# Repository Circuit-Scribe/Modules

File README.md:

Modules
=======

Eagle files for all Circuit Scribe modules!

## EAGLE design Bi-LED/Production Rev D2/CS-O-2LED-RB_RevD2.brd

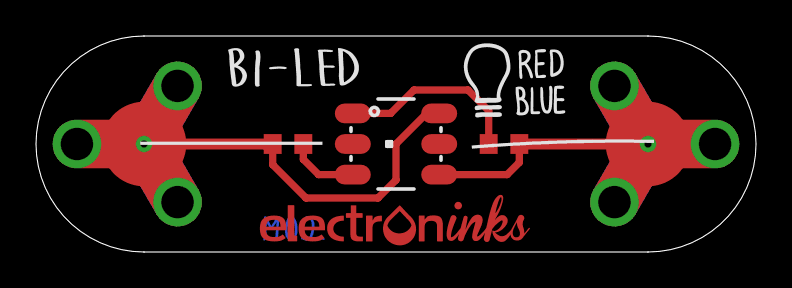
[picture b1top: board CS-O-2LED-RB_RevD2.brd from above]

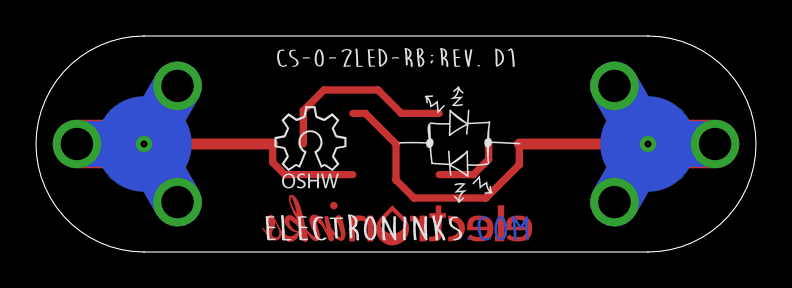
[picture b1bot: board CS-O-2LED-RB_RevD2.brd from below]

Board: 2 copper layers, 40.0 x 12.0 mm, 9 parts (3 on the bottom side), 4 nets.

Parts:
LED1: LED-TRICOLOR-5050NO_IC; LED-TRICOLOR-5050
R2-BLUE: 3.3k 5%; R0603
R_RED: 2.2k 5%; R0603
U$1, U$2: ROUND-12MM-FOOT-1.8MM; ROUND-12MM-FOOT
U$4: ELECTRONINKS_LOGO_15MM
U$5: ELECTRONINKS_COM_15MM
U$7: OSHW_4MM; OHSW_4MM
U$8: CS_O_2LED_RB

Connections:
unnamed: LED1.1, R2-BLUE.1, U$1.P$1, U$1.P$2, U$1.P$3, U$1.P$4, U$1.P$5
unnamed: LED1.6, R_RED.2
unnamed: LED1.3, R_RED.1, U$2.P$1
unnamed: LED1.4, R2-BLUE.2

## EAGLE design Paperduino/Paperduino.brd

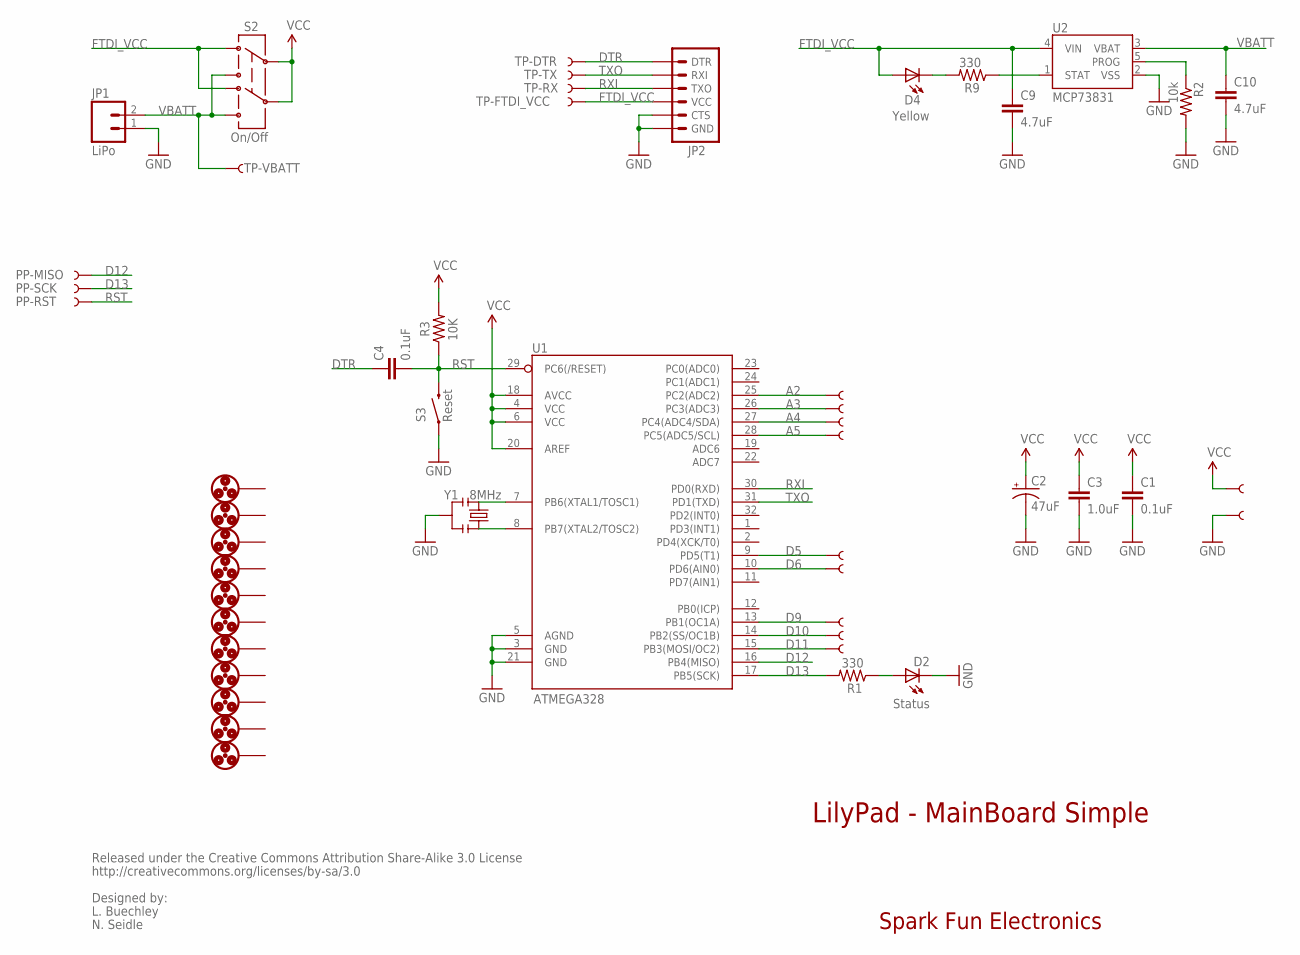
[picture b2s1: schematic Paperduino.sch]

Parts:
A2/16, A3/17, A4/18, A5/19: SEWTAP9; PETAL-LONG-1-2SIDE
C1, C4: 0.1uF; 0402-CAP
C2: 47uF; EIA3528
C3: 1.0uF; 0402-CAP
C9, C10: 4.7uF; 0402-CAP
D2: Status; LED-0603
D4: Yellow; LED-0603
JP1: LiPo; JST-2-SMD
JP2: ARDUINO_SERIAL_PROGRAMSMD; 1X06-SMD
PP-MISO: TEST-POINT3X5; PAD.03X.05
PP-RST: TEST-POINT3X5; PAD.03X.05
PP-SCK: TEST-POINT3X5; PAD.03X.05
R1, R9: 330; 0402-RES
R2: 10k; 0402-RES
R3: 10K; 0402-RES
S2: On/Off; AYZ0202
S3: Reset; TACTILE_SWITCH_SMD
TP-DTR: TEST-POINT3X5; PAD.03X.05
TP-FTDI_VCC: TEST-POINT3X5; PAD.03X.05
TP-RX: TEST-POINT3X5; PAD.03X.05
TP-TX: TEST-POINT3X5; PAD.03X.05
TP-VBATT: TEST-POINT3X5; PAD.03X.05
U1: ATMEGA328; TQFP32-08
U2: MCP73831; SOT23-5
U$1, U$2, U$3, U$5, U$6, U$7, U$8, U$9, U$10, U$11, U$12: ROUND-12MM-FOOT-1.8MM; ROUND-12MM-FOOT
U$4, U$35, U$37, U$39, U$41, U$43, U$45: SEWTAP9; PETAL-LONG-1-2SIDE
Y1: 8MHz; RESONATOR-SMD

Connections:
A2: A2/16.1, U1.25 (PC2(ADC2))
A3: A3/17.1, U1.26 (PC3(ADC3))
A4: A4/18.1, U1.27 (PC4(ADC4/SDA))
A5: A5/19.1, U1.28 (PC5(ADC5/SCL))
D5: U1.9 (PD5(T1)), U$41.1
D6: U1.10 (PD6(AIN0)), U$35.1
D9: U1.13 (PB1(OC1A)), U$37.1
D10: U1.14 (PB2(SS/OC1B)), U$39.1
D11: U1.15 (PB3(MOSI/OC2)), U$4.1
D12: PP-MISO.P$1, U1.16 (PB4(MISO))
D13: PP-SCK.P$1, R1.2, U1.17 (PB5(SCK))
DTR: C4.1, JP2.1 (DTR), TP-DTR.P$1
FTDI_VCC: C9.1, D4.A, JP2.4 (VCC), S2.3 (1), S2.6 (4), TP-FTDI_VCC.P$1, U2.4 (VIN)
GND: C1.2, C2.C (-), C3.2, C9.2, C10.2, D2.C, JP1.1, JP2.5 (CTS), JP2.6 (GND), R2.2, S3.1, U1.3 (GND), U1.5 (AGND), U1.21 (GND), U2.2 (VSS), U$43.1, Y1.2
unnamed: U1.7 (PB6(XTAL1/TOSC1)), Y1.1
unnamed: D2.A, R1.1
unnamed: U1.8 (PB7(XTAL2/TOSC2)), Y1.3
unnamed: D4.C, R9.2
PROG: R2.1, U2.5 (PROG)
RST: C4.2, PP-RST.P$1, R3.1, S3.3 (2), U1.29 (PC6(/RESET))
RXI: JP2.3 (TXO), TP-RX.P$1, U1.30 (PD0(RXD))
STAT: R9.1, U2.1 (STAT)
TXO: JP2.2 (RXI), TP-TX.P$1, U1.31 (PD1(TXD))
VBATT: C10.1, JP1.2, S2.1 (3), S2.4 (6), TP-VBATT.P$1, U2.3 (VBAT)
VCC: C1.1, C2.A (+), C3.1, R3.2, S2.2, S2.5, U1.4 (VCC), U1.6 (VCC), U1.18 (AVCC), U1.20 (AREF), U$45.1

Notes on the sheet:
LilyPad - MainBoard Simple
Spark Fun Electronics
Released under the Creative Commons Attribution Share-Alike 3.0 License
http://creativecommons.org/licenses/by-sa/3.0
Designed by:
L. Buechley
N. Seidle

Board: 2 copper layers, 49 parts (0 on the bottom side), 25 nets, no tracks yet.

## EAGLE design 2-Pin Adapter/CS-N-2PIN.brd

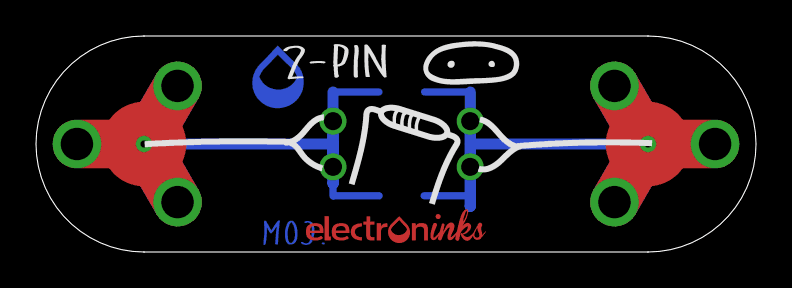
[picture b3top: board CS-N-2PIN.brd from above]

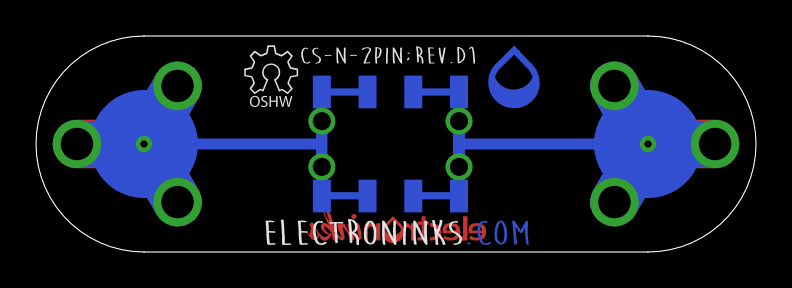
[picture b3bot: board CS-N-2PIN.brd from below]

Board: 2 copper layers, 40.0 x 12.0 mm, 8 parts (5 on the bottom side), 2 nets.

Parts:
U$1, U$2: ROUND-12MM-FOOT-1.8MM; ROUND-12MM-FOOT
U$3: DROPLET_LOGO_3MM
U$4: OSHW_3MM
U$5: ELECTRONINKS_COM_15MM
U$6: ELECTRONINKS_LOGO_10MM
U$7: C_N_2PIN; CS_N_2PIN
U$8: 966206-2000-AR-PR-SOCKET-2-PIN-6POS; 966206-2000-AR-PR-6-POS-THROUGH-HOLE

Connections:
unnamed: U$2.P$1, U$8.P$5, U$8.P$11, U$8.P$111, U$8.P$55555
unnamed: U$1.P$1, U$8.P$4, U$8.P$8

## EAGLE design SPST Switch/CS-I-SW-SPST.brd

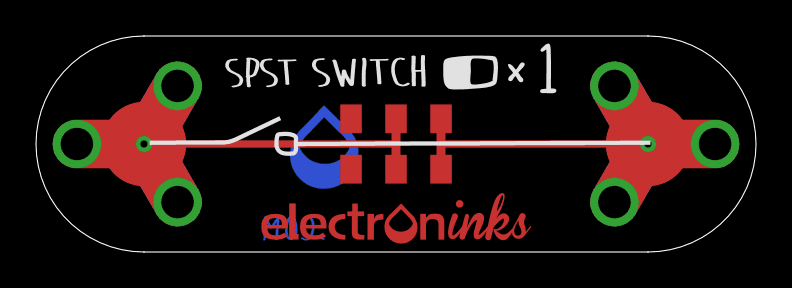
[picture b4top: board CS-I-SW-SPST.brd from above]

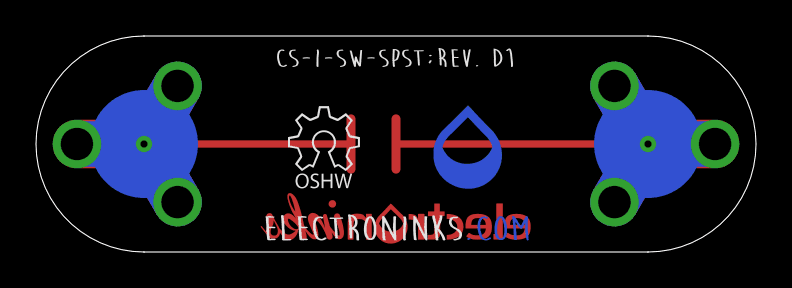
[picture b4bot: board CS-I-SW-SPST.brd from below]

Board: 2 copper layers, 40.0 x 12.0 mm, 8 parts (4 on the bottom side), 2 nets.

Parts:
U$1, U$2: ROUND-12MM-FOOT-1.8MM; ROUND-12MM-FOOT
U$3: ELECTRONINKS_LOGO_15MM
U$4: ELECTRONINKS_COM_15MM
U$5: CL-SB-22A-02T-SLIDE-SWITCH-TUCKED-PADS; CL-SB-22A-02T-DPDT-COMPACT-SWITCH
U$6: DROPLET_LOGO_4MM
U$7: OSHW_4MM; OHSW_4MM
U$8: CS_I_SW_SPST

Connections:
unnamed: U$1.P$1, U$5.P$1, U$5.P$4
unnamed: U$2.P$1, U$5.P$2, U$5.P$5

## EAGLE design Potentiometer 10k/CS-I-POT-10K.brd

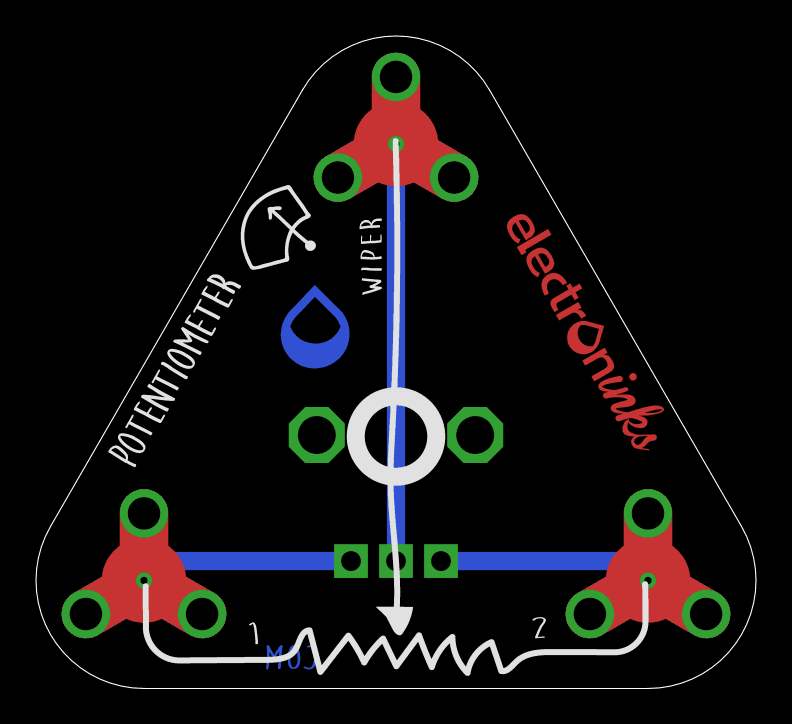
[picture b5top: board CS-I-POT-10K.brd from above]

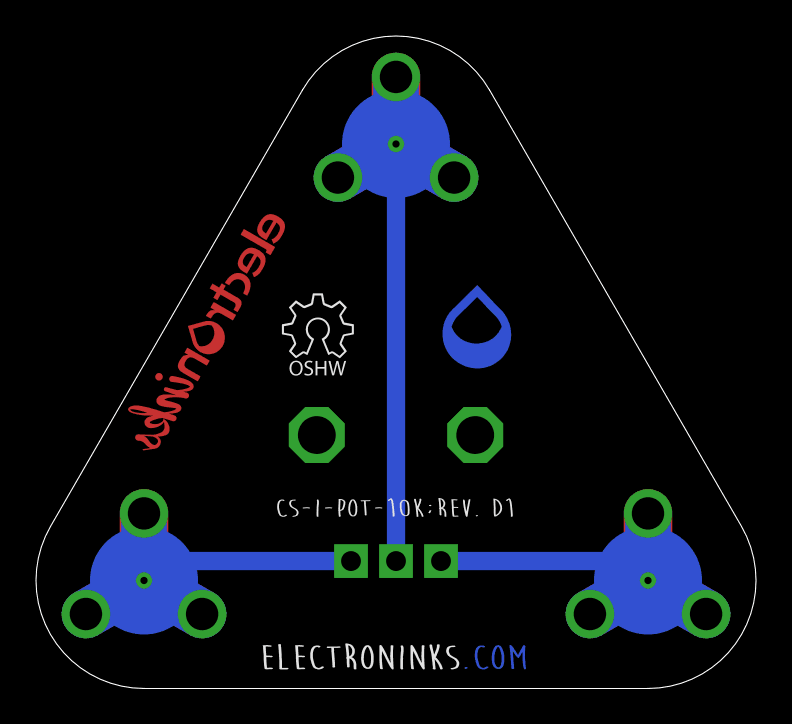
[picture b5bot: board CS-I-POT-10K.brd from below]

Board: 2 copper layers, 40.0 x 36.2 mm, 9 parts (4 on the bottom side), 3 nets.

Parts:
RV1: ALPS_POT
U$1, U$2, U$3: ROUND-12MM-FOOT-1.8MM; ROUND-12MM-FOOT
U$4: ELECTRONINKS_LOGO_15MM
U$5: ELECTRONINKS_COM_15MM
U$6: DROPLET_LOGO_4MM
U$7: OSHW_4MM; OHSW_4MM
U$8: CS_I_POT_10K

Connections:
unnamed: RV1.P$3, U$1.P$1, U$1.P$2, U$1.P$3, U$1.P$4, U$1.P$5
unnamed: RV1.P$1, U$3.P$1, U$3.P$2, U$3.P$3, U$3.P$4, U$3.P$5
unnamed: RV1.P$2, U$2.P$1, U$2.P$2, U$2.P$3, U$2.P$4, U$2.P$5

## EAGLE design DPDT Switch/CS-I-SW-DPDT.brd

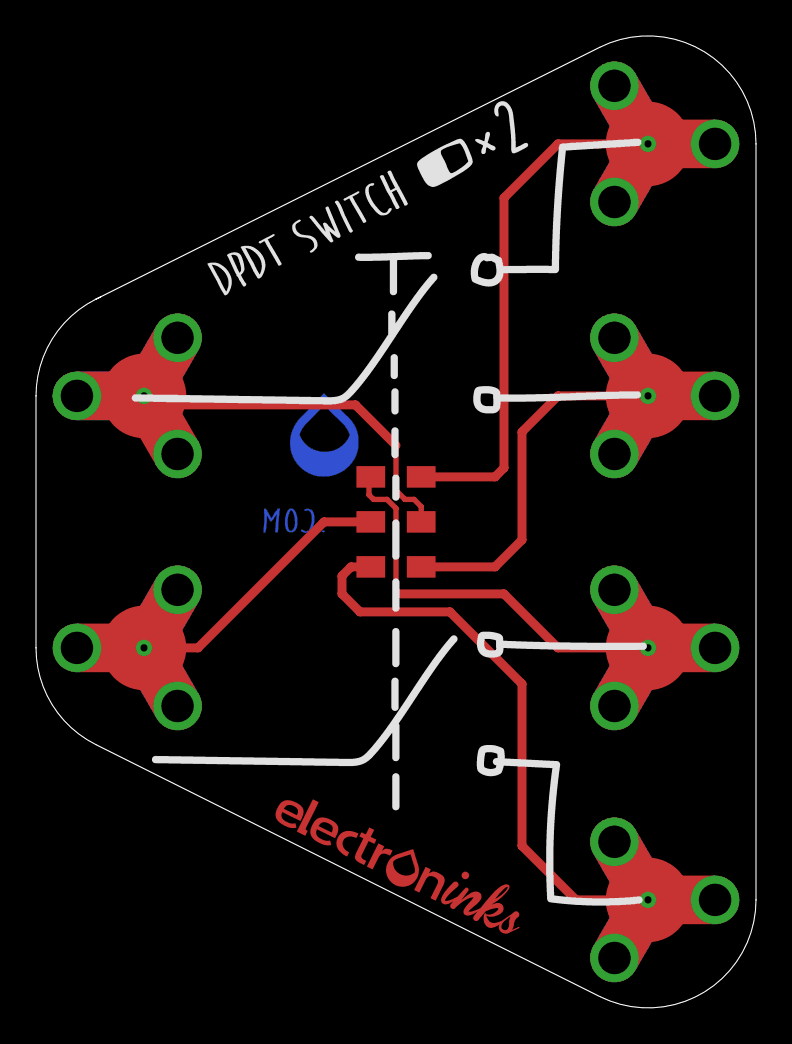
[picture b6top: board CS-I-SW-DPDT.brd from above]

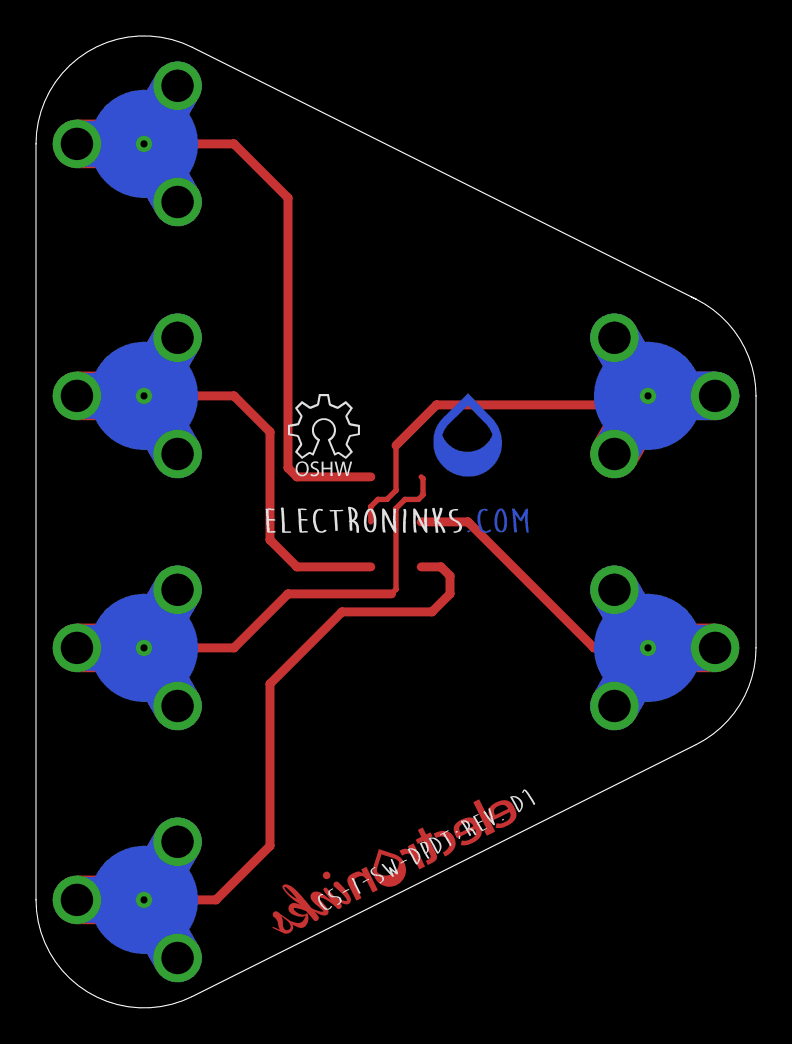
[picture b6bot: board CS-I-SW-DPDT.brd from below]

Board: 2 copper layers, 40.0 x 54.0 mm, 12 parts (4 on the bottom side), 6 nets.

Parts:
U$1, U$2, U$3, U$4, U$5, U$6: ROUND-12MM-FOOT-1.8MM; ROUND-12MM-FOOT
U$7: CL-SB-22A-02T-SLIDE-SWITCH-TUCKED-PADS; CL-SB-22A-02T-DPDT-COMPACT-SWITCH
U$8: ELECTRONINKS_LOGO_15MM
U$9: ELECTRONINKS_COM_15MM
U$10: OSHW_4MM; OHSW_4MM
U$11: DROPLET_LOGO_4MM
U$12: CS_I_SW_DPDT

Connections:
unnamed: U$1.P$1, U$7.P$5
unnamed: U$4.P$1, U$7.P$2
unnamed: U$2.P$1, U$7.P$6
unnamed: U$5.P$1, U$7.P$3
unnamed: U$3.P$1, U$7.P$4
unnamed: U$6.P$1, U$7.P$1

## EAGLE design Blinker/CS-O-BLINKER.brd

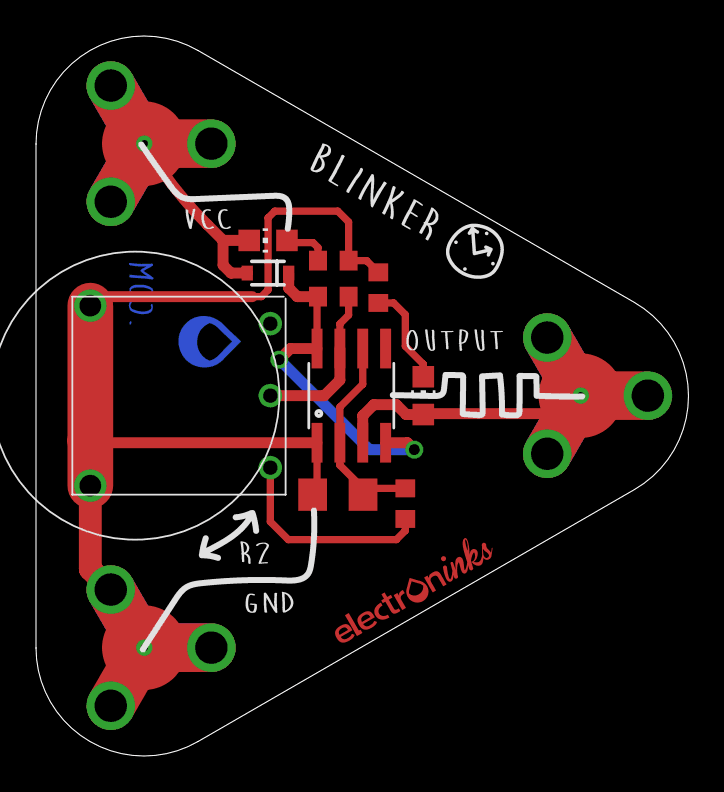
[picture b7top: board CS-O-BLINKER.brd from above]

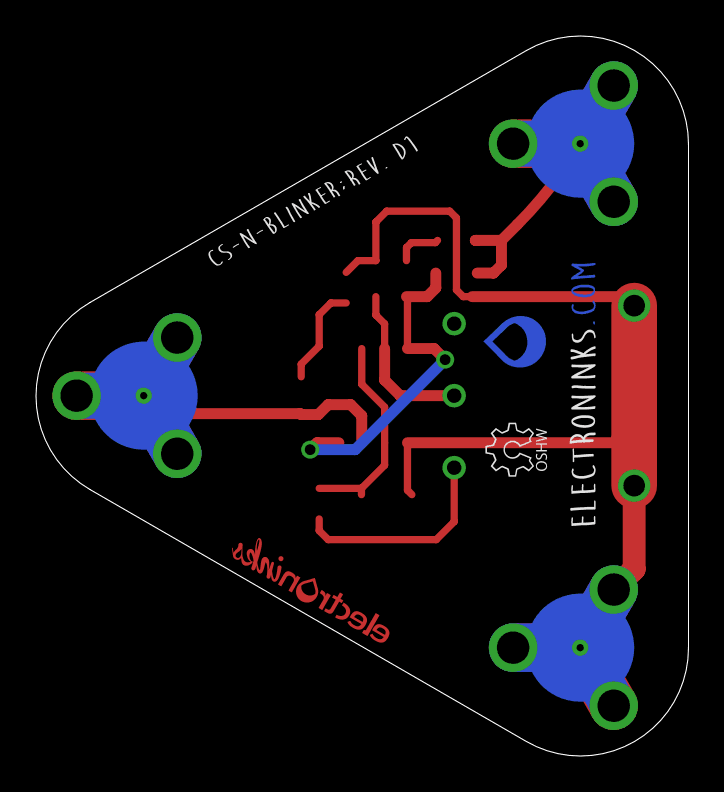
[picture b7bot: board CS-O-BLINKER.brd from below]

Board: 2 copper layers, 36.2 x 40.0 mm, 18 parts (4 on the bottom side), 9 nets.

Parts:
C1: 10uf; C1206
D1: SOD323 DIODE SCHOTTKY 20V 300MA USC; SOD-323
IC1: TLC555; SO08
LED1: Green; CHIP-LED0805
LED2: RED; CHIP-LED0805
R1, R2: 10k; R0603
R3: 1k; R0603
R4: 5k; R0603
U$1, U$2, U$3: ROUND-12MM-FOOT-1.8MM; ROUND-12MM-FOOT
U$4: WH141-THUMB-POT-500K; WH0141
U$5: ELECTRONINKS_LOGO_10MM
U$6: DROPLET_LOGO_3MM
U$7: ELECTRONINKS_COM_15MM
U$8: OSHW_3MM
U$9: CS_N_BLINKER

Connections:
GND: C1.2, IC1.1, R1.1, R2.1, U$2.P$1, U$2.P$2, U$2.P$3, U$2.P$4, U$2.P$5, U$4.P$1, U$4.P$2
unnamed: IC1.7, R3.1, U$4.P$4
unnamed: C1.1, IC1.2, IC1.6, R4.1
unnamed: IC1.3, LED1.A, U$3.P$1, U$3.P$2, U$3.P$3, U$3.P$4, U$3.P$5
unnamed: LED2.A, R2.2
unnamed: LED1.C, R1.2
unnamed: R4.2, U$4.P$3
unnamed: D1.2, LED2.C, U$1.P$1, U$1.P$2, U$1.P$3, U$1.P$4, U$1.P$5
VCC: D1.1, IC1.4, IC1.8, R3.2

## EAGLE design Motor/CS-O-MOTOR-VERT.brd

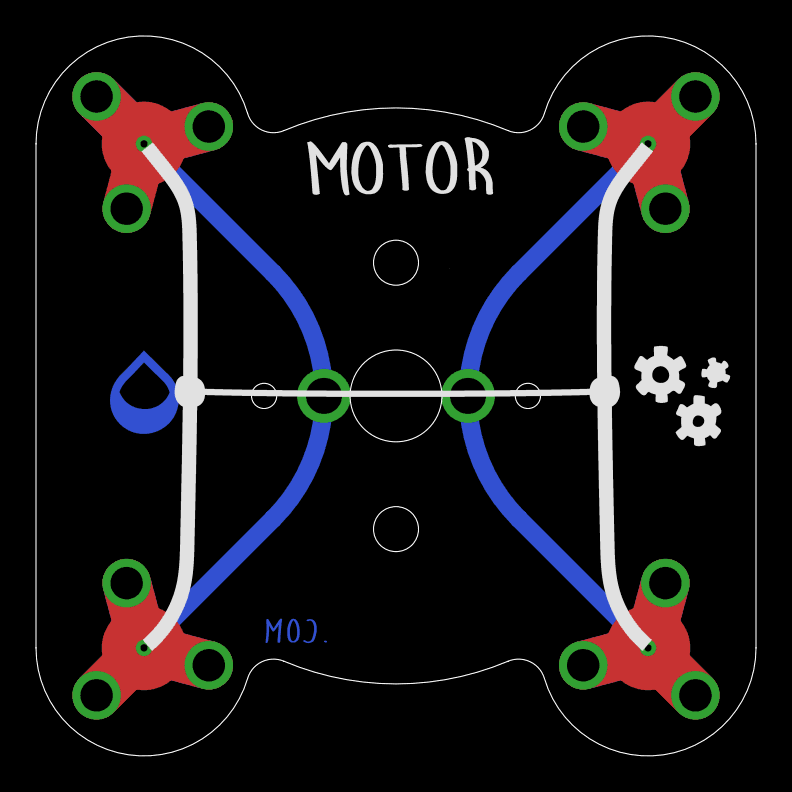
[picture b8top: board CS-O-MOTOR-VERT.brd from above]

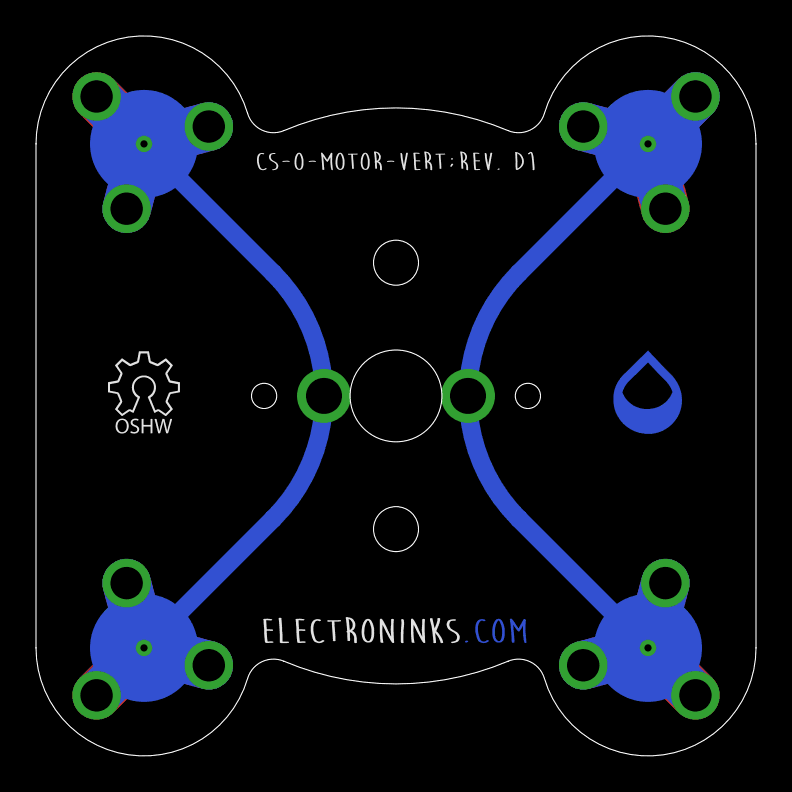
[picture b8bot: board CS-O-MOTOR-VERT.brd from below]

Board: 2 copper layers, 40.0 x 40.0 mm, 8 parts (4 on the bottom side), 2 nets.

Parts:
U$1, U$2, U$3, U$4: ROUND-12MM-FOOT-1.8MM; ROUND-12MM-FOOT
U$5: DROPLET_LOGO_4MM
U$6: OSHW_4MM; OHSW_4MM
U$7: ELECTRONINKS_COM_15MM
U$8: CS_O_MOTOR_VERT

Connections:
unnamed: U$1.P$1, U$2.P$1
unnamed: U$3.P$1, U$4.P$1

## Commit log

2014-08-07 First public revision
2014-12-23 Paperduino Initial Layout
    Started on an Arduino
2014-12-24 LEDs using 5050s

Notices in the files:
parts and their libraries:
SparkFun-LED: Licensing: Creative Commons ShareAlike 4.0 International - https://creativecommons.org/licenses/by-sa/4.0
